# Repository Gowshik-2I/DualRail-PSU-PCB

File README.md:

# ⚡ DualRail-PSU-PCB

> A compact dual-output regulated power supply PCB delivering **5V @ 1A** and **3.3V @ 1A** from a wide input range of **7V to 40V DC**.

---

## 📌 Overview

DualRail-PSU-PCB is a beginner-to-intermediate level PCB design project built using **KiCad 9.0**. It takes an unregulated DC input and provides two clean, stable regulated outputs — perfect for powering microcontrollers, sensors, and embedded systems like Arduino, ESP32, and STM32.

This is a **portfolio/learning project** designed to demonstrate PCB design skills including schematic capture, component selection, layout, and design rule checking.

---

## ✨ Features

- 🔌 Wide input range: **7V to 40V DC**
- ⚡ Dual regulated outputs: **5V @ 1A** and **3.3V @ 1A**
- 🛡️ Reverse polarity protection via **1N5819 Schottky diode**
- 💡 Input power indicator LED
- 💡 Output indicator LEDs for both 5V and 3.3V rails
- 🔩 Screw terminal connectors for easy wiring
- 🧲 Compact PCB form factor
- ✅ Designed and verified in KiCad 9.0

---

## 🔧 Specifications

| Parameter | Value |
|---|---|
| Input Voltage | 7V – 40V DC |
| Output 1 | 5V @ 1A |
| Output 2 | 3.3V @ 1A |
| Regulator 1 | LM7805 (TO-220) |
| Regulator 2 | AMS1117-3.3 (SOT-223) |
| Protection | Reverse polarity (1N5819) |
| PCB Layers | 2 (F.Cu + B.Cu) |
| PCB Size | ~90mm x 50mm |
| Designed With | KiCad 9.0 |

---

## 🗂️ Schematic Explanation

### 1. Input Stage
- **J1** — 2-pin screw terminal accepts 7V–40V DC input
- **D1 (1N5819)** — Schottky diode provides reverse polarity protection with minimal voltage drop
- **C3 (0.33µF)** and **C1 (0.1µF)** — Input filter capacitors to clean incoming supply noise
- **PWR_FLAG** — Tells KiCad ERC that this net is externally driven

### 2. Input Indicator LED
- Zener clamp circuit with resistor + LED indicates input power presence
- Works across full 7V–40V range without burning the LED

### 3. 5V Regulation Stage
- **U1 (LM7805 TO-220)** — Linear voltage regulator, outputs fixed 5V
- **C2 (10µF)** — Bulk output capacitor for load transient response
- **C4 (0.1µF)** — High frequency bypass capacitor
- **R1 (330Ω) + D2 (LED)** — 5V output indicator

### 4. 3.3V Regulation Stage
- **U2 (AMS1117-3.3 SOT-223)** — LDO regulator powered from 5V rail
- Input taken from 5V output — minimizes heat dissipation across U2
- **C5 (10µF)** — Mandatory output stability capacitor (required by AMS1117)
- **C6 (0.1µF)** — High frequency bypass capacitor
- **R2 (100Ω) + D3 (LED)** — 3.3V output indicator

### 5. Output Connectors
- **J2** — 2-pin screw terminal for 5V output
- **J3** — 2-pin screw terminal for 3.3V output

---

## 🔌 How to Use / Connect

### Step 1: Connect Input Power
```
J1 Pin 1 → Positive (+) of your DC supply (7V to 40V)
J1 Pin 2 → Negative (−) / Ground
```

### Step 2: Connect Your Load
```
5V Output:
  J2 Pin 1 → 5V positive to your device VCC
  J2 Pin 2 → GND

3.3V Output:
  J3 Pin 1 → 3.3V positive to your device VCC
  J3 Pin 2 → GND
```

### Step 3: Power On
```
✅ 5V LED lights up     → 5V rail is active
✅ 3.3V LED lights up   → 3.3V rail is active
```

### ⚠️ Warnings
- Never exceed **40V** input
- Always use a suitable **Heatsink** for optimal performance
- Never draw more than **1A** from either output simultaneously without heatsink on U1
- Always verify polarity before connecting — reverse polarity diode protects but it's good practice

---

## 🚀 Future Improvements

- [ ] Add **adjustable output voltage** using LM317 instead of fixed LM7805
- [ ] Switch to **switching regulator (LM2596)** for better efficiency at high input voltages
- [ ] Add **USB Type-C output** (5V/3A) for modern devices
- [ ] Add **short circuit protection** with fuse or current limiting
- [ ] Add **voltage display** using 7-segment or OLED
- [ ] Design **SMD version** for compact form factor
- [ ] Add **overcurrent indicator LED**
- [ ] Design enclosure/case for the board

---

## 🛠️ Tools Used

| Tool | Purpose |
|---|---|
| KiCad 9.0 | Schematic + PCB design |
| ngspice (KiCad built-in) | SPICE simulation |
| KiCad 3D Viewer | PCB visualization |

---

## 📚 References

- [LM7805 Datasheet — Texas Instruments](https://www.ti.com/lit/ds/symlink/lm7805.pdf)
- [AMS1117 Datasheet — Advanced Monolithic Systems](http://www.advanced-monolithic.com/pdf/ds1117.pdf)
- [1N5819 Datasheet — Vishay](http://www.vishay.com/docs/88525/1n5817.pdf)
- [KiCad Documentation](https://docs.kicad.org)

---

## 👤 Author

**Gowsh**
- GitHub: [@Gowshik-21](https://github.com/Gowshik-2I)
- LinkedIn: [Gowshik Babu D](https://www.linkedin.com/in/gowshik-babu-d-154b30313)

---

## 📄 License

This project is open source under the [MIT License](LICENSE).

Feel free to use, modify, and distribute for personal or commercial projects.

---

*Designed with ❤️ using KiCad 9.0*

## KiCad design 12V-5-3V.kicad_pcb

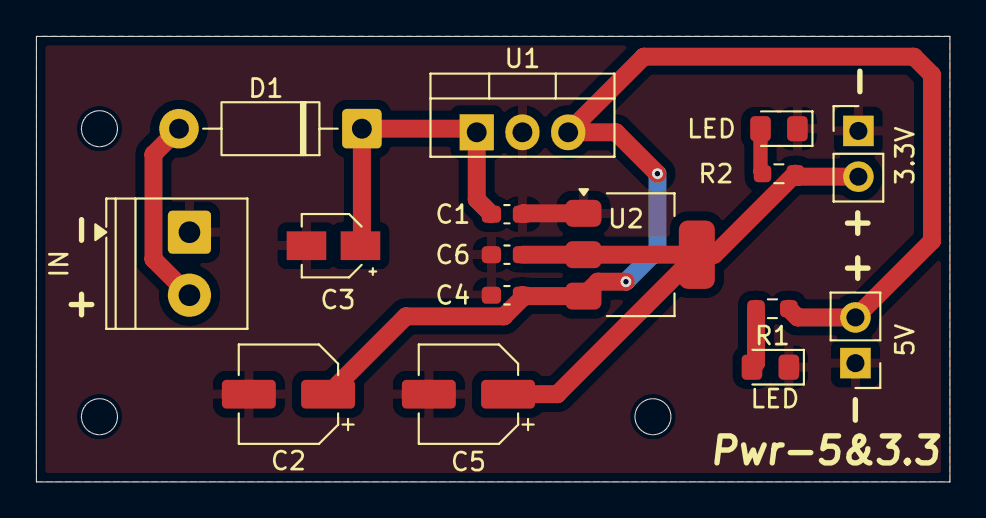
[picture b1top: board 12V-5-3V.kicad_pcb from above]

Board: 2 copper layers, 50.8 x 24.8 mm, 19 parts (0 on the bottom side), 7 nets.

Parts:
3.3V, 5V: Conn_01x02_Pin; PinHeader_1x02_P2.54mm_Vertical
C1, C4, C6: 0.1uF; C_0603_1608Metric_Pad1.08x0.95mm_HandSolder
C2, C5: 10uF; CP_Elec_5x4.4
C3: 0.33uF; CP_Elec_3x5.3
D1: 1N5819; D_DO-41_SOD81_P10.16mm_Horizontal
H1, H2, H3: MountingHole; MountingHole_2mm
IN: Screw_Terminal_01x02; TerminalBlock_Phoenix_PT-1,5-2-3.5-H_1x02_P3.50mm_Horizontal
LED: LED; LED_0805_2012Metric_Pad1.15x1.40mm_HandSolder
LED#2: LED; LED_0805_2012Metric_Pad1.15x1.40mm_HandSolder
R1: 330; R_0603_1608Metric_Pad0.98x0.95mm_HandSolder
R2: 100; R_0603_1608Metric_Pad0.98x0.95mm_HandSolder
U1: LM7805_TO220; TO-220-3_Vertical
U2: AMS1117-3.3; SOT-223-3_TabPin2

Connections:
/in: C1.1, C3.1, D1.1 (K), U1.1 (VI)
/out: 5V.2, C2.1, C4.1, R1.1, U1.3 (VO), U2.3 (VI)
/out3.3: 3.3V.2, C5.1, C6.1, R2.1, U2.2 (VO)
GND: 3.3V.1, 5V.1, C1.2, C2.2, C3.2, C4.2, C5.2, C6.2, IN.1, LED.1 (K), LED#2.1 (K), U1.2 (GND), U2.1 (GND)
unnamed: LED.2 (A), R1.2
unnamed: LED#2.2 (A), R2.2
VCC: D1.2 (A), IN.2

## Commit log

2026-04-30 Initial commit: KiCad PCB design
2026-04-30 Add .gitignore and remove backup files
2026-04-30 Initialize README.md with project details
    Added detailed project description, features, specifications, usage instructions, and author information to README.md.
2026-04-30 Create images
2026-04-30 Rename images/Screenshot 2026-04-26 001407.png to 3d_render.png
2026-04-30 initial commit
    Updated image format for PCB 3D render in README.
